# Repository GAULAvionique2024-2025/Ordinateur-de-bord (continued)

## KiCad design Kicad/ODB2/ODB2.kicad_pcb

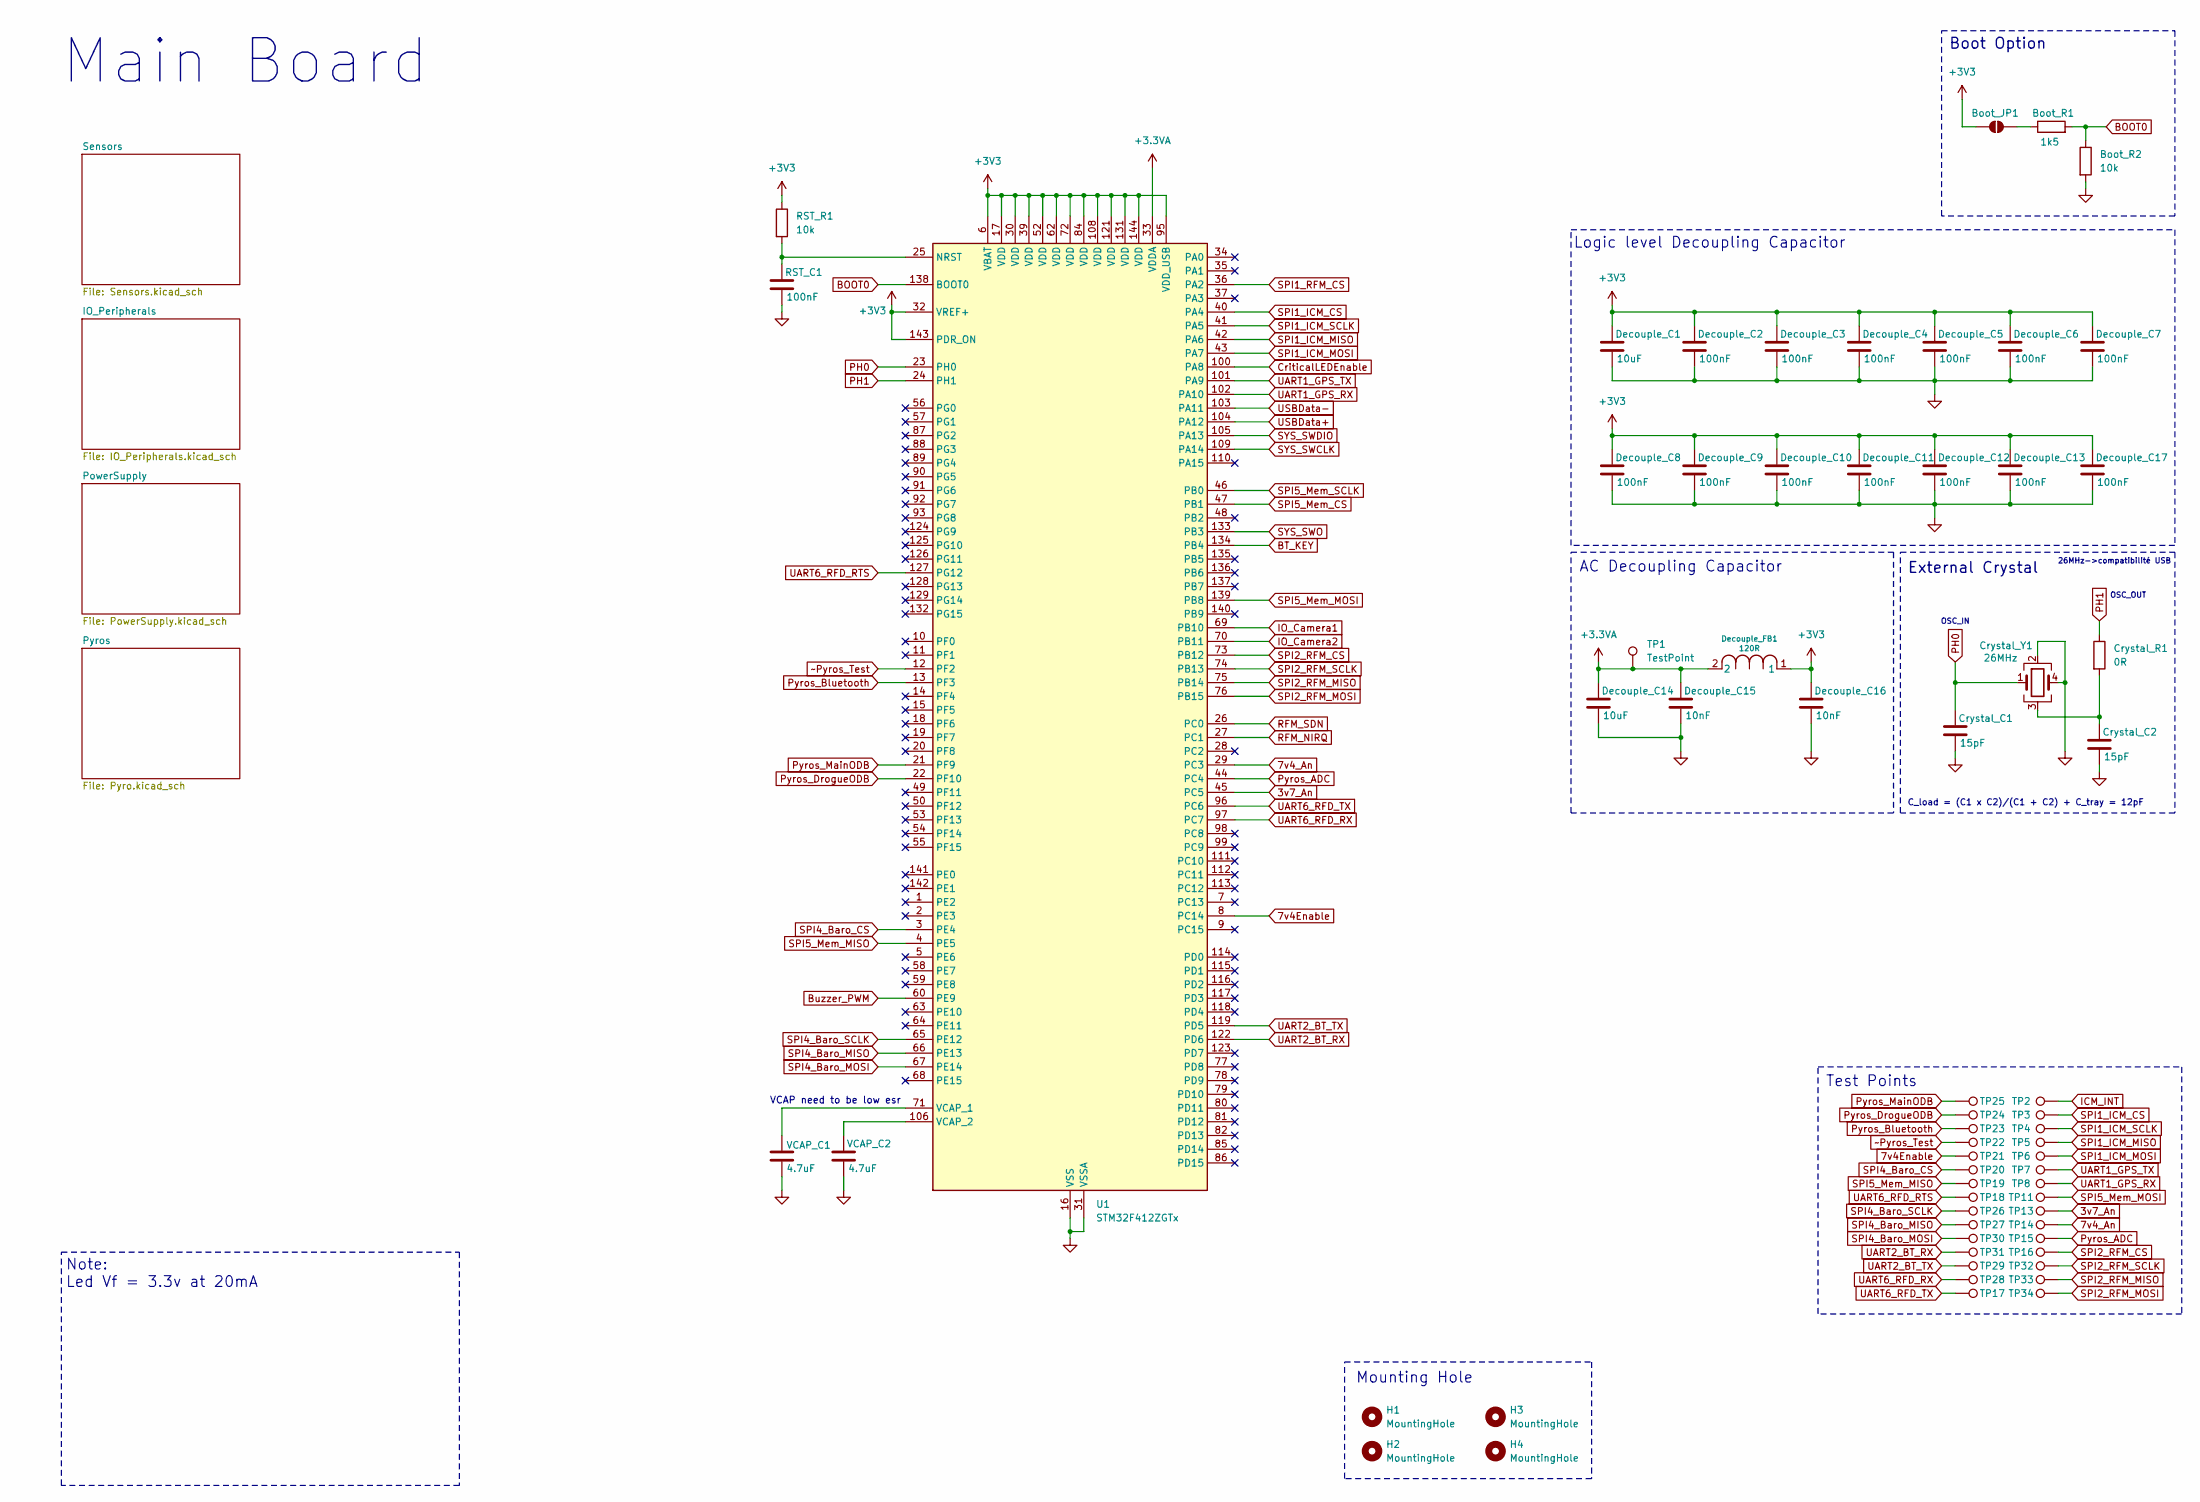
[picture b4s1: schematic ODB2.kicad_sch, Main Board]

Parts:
Boot_JP1: SolderJumper_2_Open; SolderJumper-2_P1.3mm_Open_TrianglePad1.0x1.5mm
Boot_R1: 1k5; R_0603_1608Metric
Boot_R2: 10k; R_0603_1608Metric
Crystal_C1, Crystal_C2: 15pF; C_0603_1608Metric
Crystal_R1: 0R; R_0603_1608Metric
Crystal_Y1: 26MHz; XTAL_TSX-3225_26.0000MF09Z-AC0
Decouple_C1, Decouple_C14: 10uF; C_0603_1608Metric
Decouple_C2, Decouple_C3, Decouple_C4, Decouple_C5, Decouple_C6, Decouple_C7, Decouple_C8, Decouple_C9, Decouple_C10, Decouple_C11, Decouple_C12, Decouple_C13, Decouple_C17: 100nF; C_0603_1608Metric
Decouple_C15, Decouple_C16: 10nF; C_0603_1608Metric
Decouple_FB1: 120R; IND_25_0805_FRT
H1, H2, H3, H4: MountingHole; MountingHole_4.3mm_M4
RST_C1: 100nF; C_0603_1608Metric
RST_R1: 10k; R_0603_1608Metric
TP1, TP2, TP3, TP4, TP5, TP6, TP7, TP8, TP11, TP13, TP14, TP15, TP16, TP17, TP18, TP19, TP20, TP21, TP22, TP23, TP24, TP25, TP26, TP27, TP28, TP29, TP30, TP31, TP32, TP33, TP34: TestPoint; TestPoint_Pad_D1.0mm
U1: STM32F412ZGTx; LQFP-144_20x20mm_P0.5mm
VCAP_C1, VCAP_C2: 4.7uF; C_0603_1608Metric

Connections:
3v7_An: TP13.1, U1.45 (PC5); also elsewhere on the board
7v4Enable: TP21.1, U1.8 (PC14); also elsewhere on the board
7v4_An: TP14.1, U1.29 (PC3); also elsewhere on the board
+3.3VA: Decouple_C14.1, Decouple_C15.1, Decouple_FB1.2, TP1.1, U1.33 (VDDA)
+3V3: Boot_JP1.1 (A), Decouple_C1.1, Decouple_C2.1, Decouple_C3.1, Decouple_C4.1, Decouple_C5.1, Decouple_C6.1, Decouple_C7.1, Decouple_C8.1, Decouple_C9.1, Decouple_C10.1, Decouple_C11.1, Decouple_C12.1, Decouple_C13.1, Decouple_C16.1, Decouple_C17.1, Decouple_FB1.1, RST_R1.1, U1.6 (VBAT), U1.17 (VDD), U1.30 (VDD), U1.32 (VREF+), U1.39 (VDD), U1.52 (VDD), U1.62 (VDD), U1.72 (VDD), U1.84 (VDD), U1.95 (VDD_USB), U1.108 (VDD), U1.121 (VDD), U1.131 (VDD), U1.143 (PDR_ON), U1.144 (VDD); also elsewhere on the board
BOOT0: Boot_R1.2, Boot_R2.1, U1.138 (BOOT0)
BT_KEY: U1.134 (PB4); also elsewhere on the board
Buzzer_PWM: U1.60 (PE9); also elsewhere on the board
CriticalLEDEnable: U1.100 (PA8); also elsewhere on the board
GND: Boot_R2.2, Crystal_C1.2, Crystal_C2.2, Crystal_Y1.2, Crystal_Y1.4, Decouple_C1.2, Decouple_C2.2, Decouple_C3.2, Decouple_C4.2, Decouple_C5.2, Decouple_C6.2, Decouple_C7.2, Decouple_C8.2, Decouple_C9.2, Decouple_C10.2, Decouple_C11.2, Decouple_C12.2, Decouple_C13.2, Decouple_C14.2, Decouple_C15.2, Decouple_C16.2, Decouple_C17.2, RST_C1.2, U1.16 (VSS), U1.31 (VSSA), U1.38 (VSS), U1.51 (VSS), U1.61 (VSS), U1.83 (VSS), U1.94 (VSS), U1.107 (VSS), U1.120 (VSS), U1.130 (VSS), VCAP_C1.2, VCAP_C2.2; also elsewhere on the board
ICM_INT: TP2.1
IO_Camera1: U1.69 (PB10)
IO_Camera2: U1.70 (PB11)
unnamed: Boot_JP1.2 (B), Boot_R1.1
unnamed: Crystal_C2.1, Crystal_R1.2, Crystal_Y1.3
unnamed: RST_C1.1, RST_R1.2, U1.25 (NRST)
unnamed: U1.71 (VCAP_1), VCAP_C1.1
unnamed: U1.106 (VCAP_2), VCAP_C2.1
PH0: Crystal_C1.1, Crystal_Y1.1, U1.23 (PH0)
PH1: Crystal_R1.1, U1.24 (PH1)
Pyros_ADC: TP15.1, U1.44 (PC4); also elsewhere on the board
Pyros_Bluetooth: TP23.1, U1.13 (PF3); also elsewhere on the board
Pyros_DrogueODB: TP24.1, U1.22 (PF10); also elsewhere on the board
Pyros_MainODB: TP25.1, U1.21 (PF9); also elsewhere on the board
RFM_NIRQ: U1.27 (PC1); also elsewhere on the board
RFM_SDN: U1.26 (PC0); also elsewhere on the board
SPI1_ICM_CS: TP3.1, U1.40 (PA4); also elsewhere on the board
SPI1_ICM_MISO: TP5.1, U1.42 (PA6); also elsewhere on the board
SPI1_ICM_MOSI: TP6.1, U1.43 (PA7); also elsewhere on the board
SPI1_ICM_SCLK: TP4.1, U1.41 (PA5); also elsewhere on the board
SPI1_RFM_CS: U1.36 (PA2)
SPI2_RFM_CS: TP16.1, U1.73 (PB12); also elsewhere on the board
SPI2_RFM_MISO: TP33.1, U1.75 (PB14); also elsewhere on the board
SPI2_RFM_MOSI: TP34.1, U1.76 (PB15); also elsewhere on the board
SPI2_RFM_SCLK: TP32.1, U1.74 (PB13); also elsewhere on the board
SPI4_Baro_CS: TP20.1, U1.3 (PE4); also elsewhere on the board
SPI4_Baro_MISO: TP27.1, U1.66 (PE13); also elsewhere on the board
SPI4_Baro_MOSI: TP30.1, U1.67 (PE14); also elsewhere on the board
SPI4_Baro_SCLK: TP26.1, U1.65 (PE12); also elsewhere on the board
SPI5_Mem_CS: U1.47 (PB1); also elsewhere on the board
SPI5_Mem_MISO: TP19.1, U1.4 (PE5); also elsewhere on the board
SPI5_Mem_MOSI: TP11.1, U1.139 (PB8); also elsewhere on the board
SPI5_Mem_SCLK: U1.46 (PB0); also elsewhere on the board
SYS_SWCLK: U1.109 (PA14); also elsewhere on the board
SYS_SWDIO: U1.105 (PA13); also elsewhere on the board
SYS_SWO: U1.133 (PB3); also elsewhere on the board
UART1_GPS_RX: TP8.1, U1.102 (PA10); also elsewhere on the board
UART1_GPS_TX: TP7.1, U1.101 (PA9); also elsewhere on the board
UART2_BT_RX: TP31.1, U1.122 (PD6); also elsewhere on the board
UART2_BT_TX: TP29.1, U1.119 (PD5); also elsewhere on the board
UART6_RFD_RTS: TP18.1, U1.127 (PG12); also elsewhere on the board
UART6_RFD_RX: TP28.1, U1.97 (PC7); also elsewhere on the board
UART6_RFD_TX: TP17.1, U1.96 (PC6); also elsewhere on the board
USBData+: U1.104 (PA12); also elsewhere on the board
USBData-: U1.103 (PA11); also elsewhere on the board
~Pyros_Test: TP22.1, U1.12 (PF2); also elsewhere on the board

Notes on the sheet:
VCAP need to be low esr
26MHz->compatibilité USB
C_load = (C1 x C2)/(C1 + C2) + C_tray = 12pF
Main Board
Mounting Hole
Boot Option
Note: Led Vf = 3.3v at 20mA
AC Decoupling Capacitor
OSC_OUT
Test Points
External Crystal
Logic level Decoupling Capacitor
OSC_IN

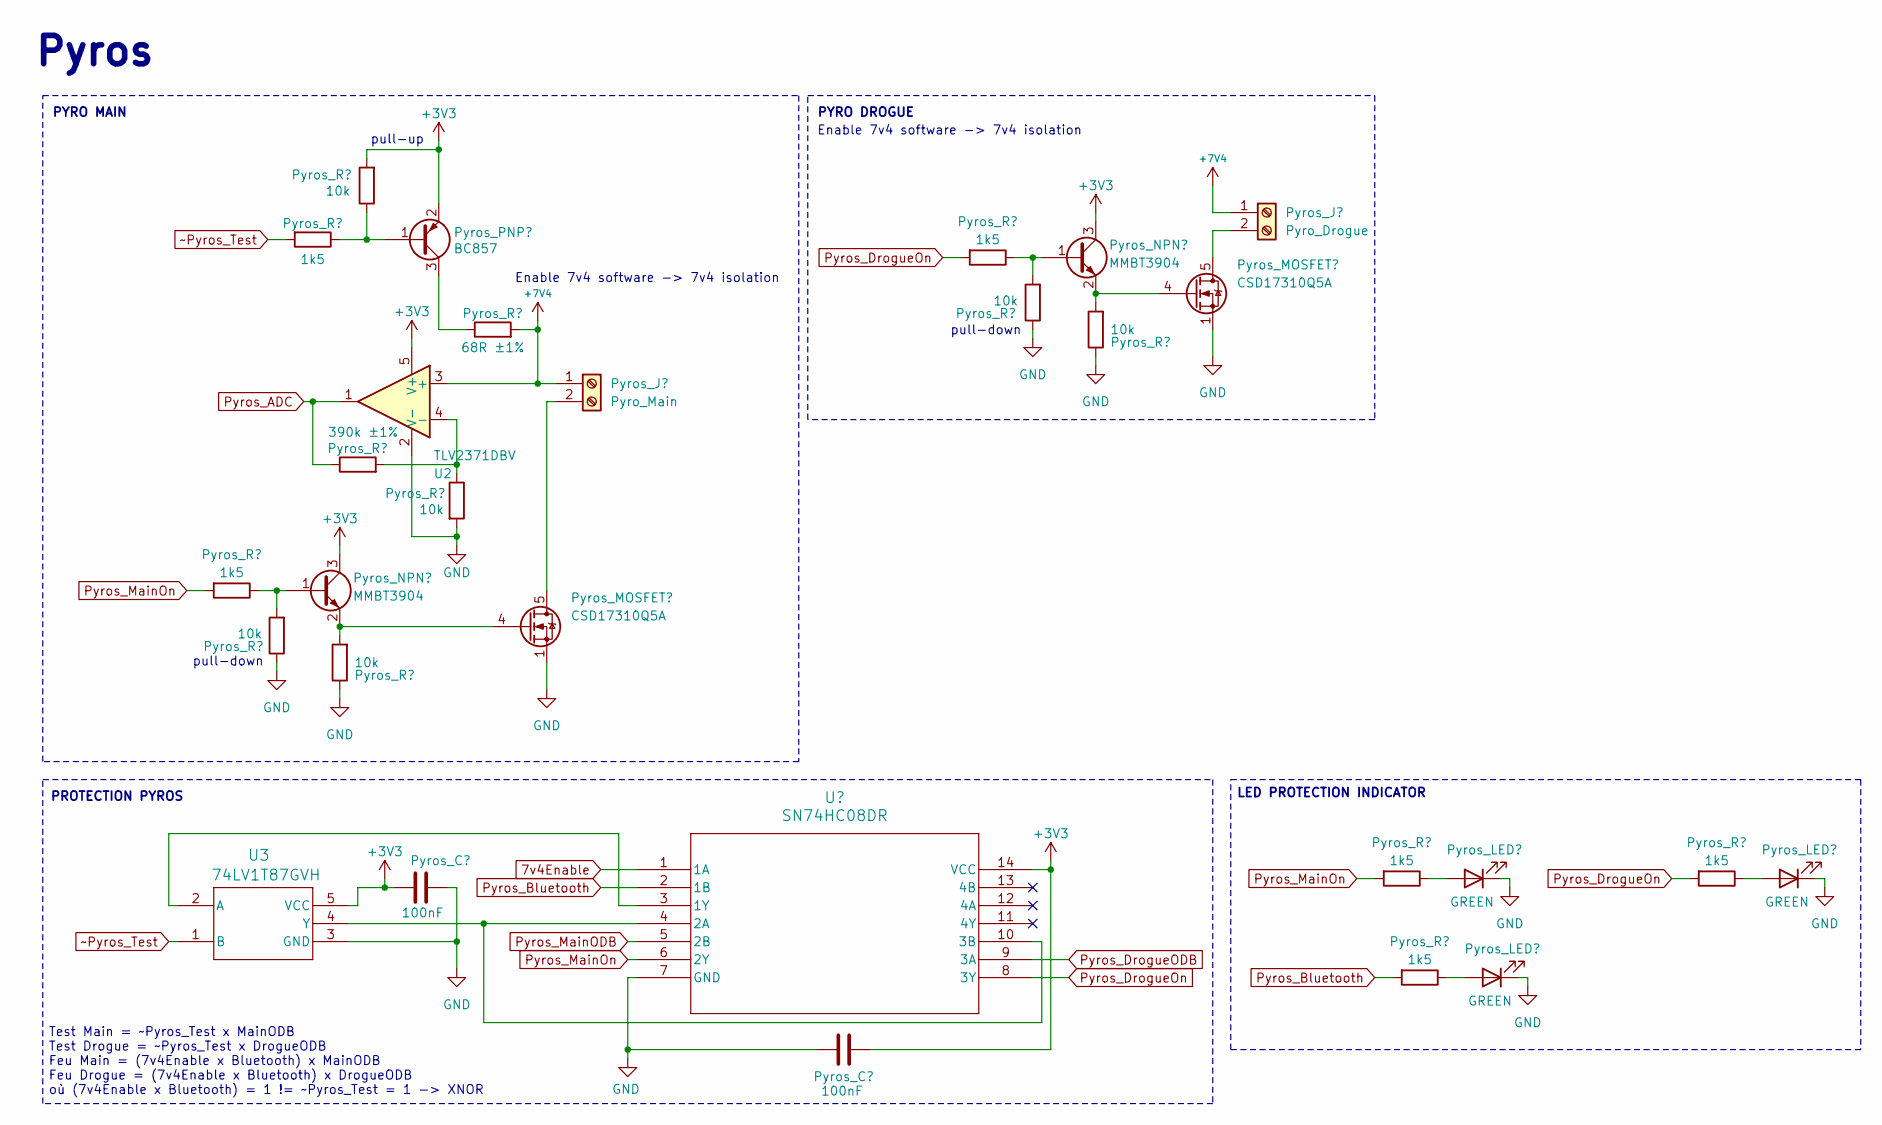
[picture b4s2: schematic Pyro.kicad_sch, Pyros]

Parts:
Pyros_AND1: SN74HC08DR; SOIC-14_3.9x8.7mm_P1.27mm
Pyros_C1, Pyros_C2: 100nF; C_0603_1608Metric
Pyros_J1: Pyro_Main; TerminalBlock_RND_205-00012_1x02_P5.00mm_Horizontal
Pyros_J2: Pyro_Drogue; TerminalBlock_RND_205-00012_1x02_P5.00mm_Horizontal
Pyros_LED1, Pyros_LED2, Pyros_LED4: GREEN; LED_0603_1608Metric
Pyros_MOSFET1, Pyros_MOSFET2: CSD17310Q5A; TDSON-8-1
Pyros_NPN1, Pyros_NPN2: MMBT3904; SOT-23
Pyros_PNP1: BC857; SOT-23
Pyros_R1, Pyros_R6, Pyros_R14, Pyros_R17, Pyros_R18, Pyros_R19: 1k5; R_0603_1608Metric
Pyros_R2, Pyros_R5, Pyros_R7, Pyros_R8, Pyros_R15, Pyros_R16: 10k; R_0603_1608Metric
Pyros_R3: 68R ±1%; R_0603_1608Metric
Pyros_R4: 390k ±1%; R_0603_1608Metric
U2: TLV2371DBV; SOT-23-5
U3: 74LV1T87GVH; SC-74A_SOT753_NEX

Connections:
7v4Enable: Pyros_AND1.1 (1A); also elsewhere on the board
+3V3: Pyros_AND1.14 (VCC), Pyros_C1.2, Pyros_C2.1, Pyros_NPN1.3 (C), Pyros_NPN2.3 (C), Pyros_PNP1.2 (E), Pyros_R2.2, U2.5 (V+), U3.5 (VCC); also elsewhere on the board
+7V4: Pyros_J1.1, Pyros_J2.1, Pyros_R3.2, U2.3 (+); also elsewhere on the board
GND: Pyros_AND1.7 (GND), Pyros_C1.1, Pyros_C2.2, Pyros_LED1.1 (K), Pyros_LED2.1 (K), Pyros_LED4.1 (K), Pyros_MOSFET1.1 (S), Pyros_MOSFET1.2 (S), Pyros_MOSFET1.3 (S), Pyros_MOSFET2.1 (S), Pyros_MOSFET2.2 (S), Pyros_MOSFET2.3 (S), Pyros_R5.2, Pyros_R7.1, Pyros_R8.1, Pyros_R15.1, Pyros_R16.1, U2.2 (V-), U3.3 (GND); also elsewhere on the board
unnamed: Pyros_AND1.3 (1Y), U3.2 (A)
unnamed: Pyros_AND1.4 (2A), Pyros_AND1.10 (3B), U3.4 (Y)
unnamed: Pyros_J1.2, Pyros_MOSFET1.5 (D)
unnamed: Pyros_J2.2, Pyros_MOSFET2.5 (D)
unnamed: Pyros_LED1.2 (A), Pyros_R17.1
unnamed: Pyros_LED2.2 (A), Pyros_R18.1
unnamed: Pyros_LED4.2 (A), Pyros_R19.1
unnamed: Pyros_MOSFET1.4 (G), Pyros_NPN1.2 (E), Pyros_R8.2
unnamed: Pyros_MOSFET2.4 (G), Pyros_NPN2.2 (E), Pyros_R16.2
unnamed: Pyros_NPN1.1 (B), Pyros_R6.1, Pyros_R7.2
unnamed: Pyros_NPN2.1 (B), Pyros_R14.1, Pyros_R15.2
unnamed: Pyros_PNP1.1 (B), Pyros_R1.1, Pyros_R2.1
unnamed: Pyros_PNP1.3 (C), Pyros_R3.1
unnamed: Pyros_R4.2, Pyros_R5.1, U2.4 (-)
Pyros_ADC: Pyros_R4.1, U2.1; also elsewhere on the board
Pyros_Bluetooth: Pyros_AND1.2 (1B), Pyros_R19.2; also elsewhere on the board
Pyros_DrogueODB: Pyros_AND1.9 (3A); also elsewhere on the board
Pyros_DrogueOn: Pyros_AND1.8 (3Y), Pyros_R14.2, Pyros_R18.2
Pyros_MainODB: Pyros_AND1.5 (2B); also elsewhere on the board
Pyros_MainOn: Pyros_AND1.6 (2Y), Pyros_R6.2, Pyros_R17.2
~Pyros_Test: Pyros_R1.2, U3.1 (B); also elsewhere on the board

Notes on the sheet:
PYRO DROGUE
pull-up
Pyros
Enable 7v4 software -> 7v4 isolation
pull-down
LED PROTECTION INDICATOR
PROTECTION PYROS
Test Main = ~Pyros_Test x MainODB Test Drogue = ~Pyros_Test x DrogueODB Feu Main = (7v4Enable x Bluetooth) x MainODB Feu Drogue = (7v4Enable x Bluetooth) x DrogueODB où (7v4Enable x Bluetooth) = 1 != ~Pyros_Test = 1 -> XNOR
PYRO MAIN

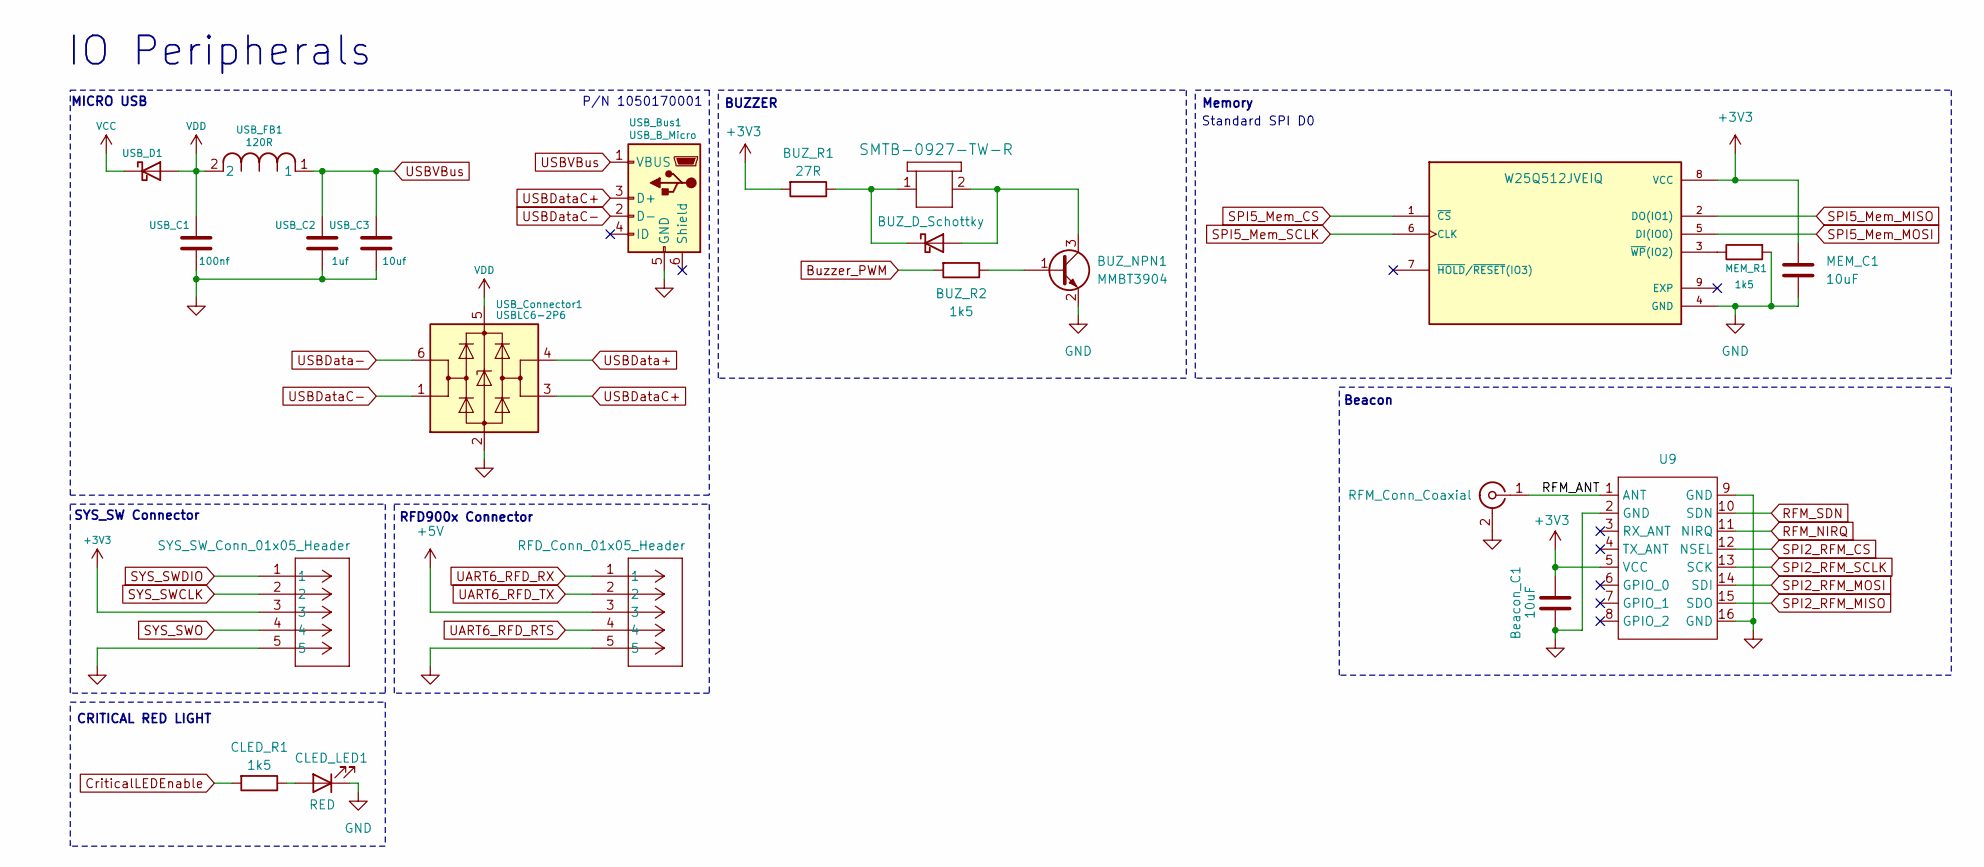
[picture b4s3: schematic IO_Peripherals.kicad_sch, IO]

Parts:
BUZ_Buzzer1: SMTB-0927-TW-R; SMTB-0927-TW-R_PUI
BUZ_NPN1: MMBT3904; SOT-23
BUZ_R1: 27R; R_0603_1608Metric
BUZ_R2: 1k5; R_0603_1608Metric
Beacon_C1: 10uF; C_0603_1608Metric
CLED_LED1: RED; LED_0603_1608Metric
CLED_R1: 1k5; R_0603_1608Metric
D3: BUZ_D_Schottky; D_SOD-123
J3: SYS_SW_Conn_01x05_Header; CONN_SDA-70543-xxxx_05_MOL
J5: RFM_Conn_Coaxial; SMA_Wurth_60312002114503_Vertical
J6: RFD_Conn_01x05_Header; CONN_SDA-70543-xxxx_05_MOL
MEM_C1: 10uF; C_0603_1608Metric
MEM_R1: 1k5; R_0603_1608Metric
U9: RFM22B; RFM22b-S2
U10: W25Q512JVEIQ; SON127P600X800X80-9N; PARTREV G
USB_Bus1: USB_B_Micro; USB_Micro-B_Molex-105017-0001
USB_C1: 100nf; C_0603_1608Metric
USB_C2: 1uf; C_0603_1608Metric
USB_C3: 10uf; C_0603_1608Metric
USB_Connector1: USBLC6-2P6; SOT-666
USB_D1: B260A-13-F; D_SOD-123
USB_FB1: 120R; IND_25_0805_FRT

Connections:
+3V3: BUZ_R1.2, Beacon_C1.2, J3.3, MEM_C1.2, U9.5 (VCC), U10.8 (VCC); also elsewhere on the board
+5V: J6.3; also elsewhere on the board
/IO_Peripherals/RFM_ANT: J5.1 (In), U9.1 (ANT)
Buzzer_PWM: BUZ_R2.2; also elsewhere on the board
CriticalLEDEnable: CLED_R1.2; also elsewhere on the board
GND: BUZ_NPN1.2 (E), Beacon_C1.1, CLED_LED1.1 (K), J3.5, J5.2 (Ext), J6.5, MEM_C1.1, MEM_R1.2, U9.2 (GND), U9.9 (GND), U9.16 (GND), U10.4 (GND), USB_Bus1.5 (GND), USB_C1.1, USB_C2.1, USB_C3.1, USB_Connector1.2 (GND); also elsewhere on the board
unnamed: BUZ_NPN1.1 (B), BUZ_R2.1
unnamed: BUZ_Buzzer1.2, BUZ_NPN1.3 (C), D3.2 (A)
unnamed: CLED_LED1.2 (A), CLED_R1.1
unnamed: BUZ_Buzzer1.1, BUZ_R1.1, D3.1 (K)
unnamed: MEM_R1.1, U10.3 (~WP(IO2))
RFM_NIRQ: U9.11 (NIRQ); also elsewhere on the board
RFM_SDN: U9.10 (SDN); also elsewhere on the board
SPI2_RFM_CS: U9.12 (NSEL); also elsewhere on the board
SPI2_RFM_MISO: U9.15 (SDO); also elsewhere on the board
SPI2_RFM_MOSI: U9.14 (SDI); also elsewhere on the board
SPI2_RFM_SCLK: U9.13 (SCK); also elsewhere on the board
SPI5_Mem_CS: U10.1 (~CS); also elsewhere on the board
SPI5_Mem_MISO: U10.2 (DO(IO1)); also elsewhere on the board
SPI5_Mem_MOSI: U10.5 (DI(IO0)); also elsewhere on the board
SPI5_Mem_SCLK: U10.6 (CLK); also elsewhere on the board
SYS_SWCLK: J3.2; also elsewhere on the board
SYS_SWDIO: J3.1; also elsewhere on the board
SYS_SWO: J3.4; also elsewhere on the board
UART6_RFD_RTS: J6.4; also elsewhere on the board
UART6_RFD_RX: J6.1; also elsewhere on the board
UART6_RFD_TX: J6.2; also elsewhere on the board
USBData+: USB_Connector1.4 (I/O2); also elsewhere on the board
USBData-: USB_Connector1.6 (I/O1); also elsewhere on the board
USBDataC+: USB_Bus1.3 (D+), USB_Connector1.3 (I/O2)
USBDataC-: USB_Bus1.2 (D-), USB_Connector1.1 (I/O1)
USBVBus: USB_Bus1.1 (VBUS), USB_C2.2, USB_C3.2, USB_FB1.1
VCC: USB_D1.1 (K); also elsewhere on the board
VDD: USB_C1.2, USB_Connector1.5 (VBUS), USB_D1.2 (A), USB_FB1.2; also elsewhere on the board

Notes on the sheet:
CRITICAL RED LIGHT
IO Peripherals
Memory
Beacon
MICRO USB
P/N 1050170001
BUZZER
Standard SPI D0
RFD900x Connector
SYS_SW Connector

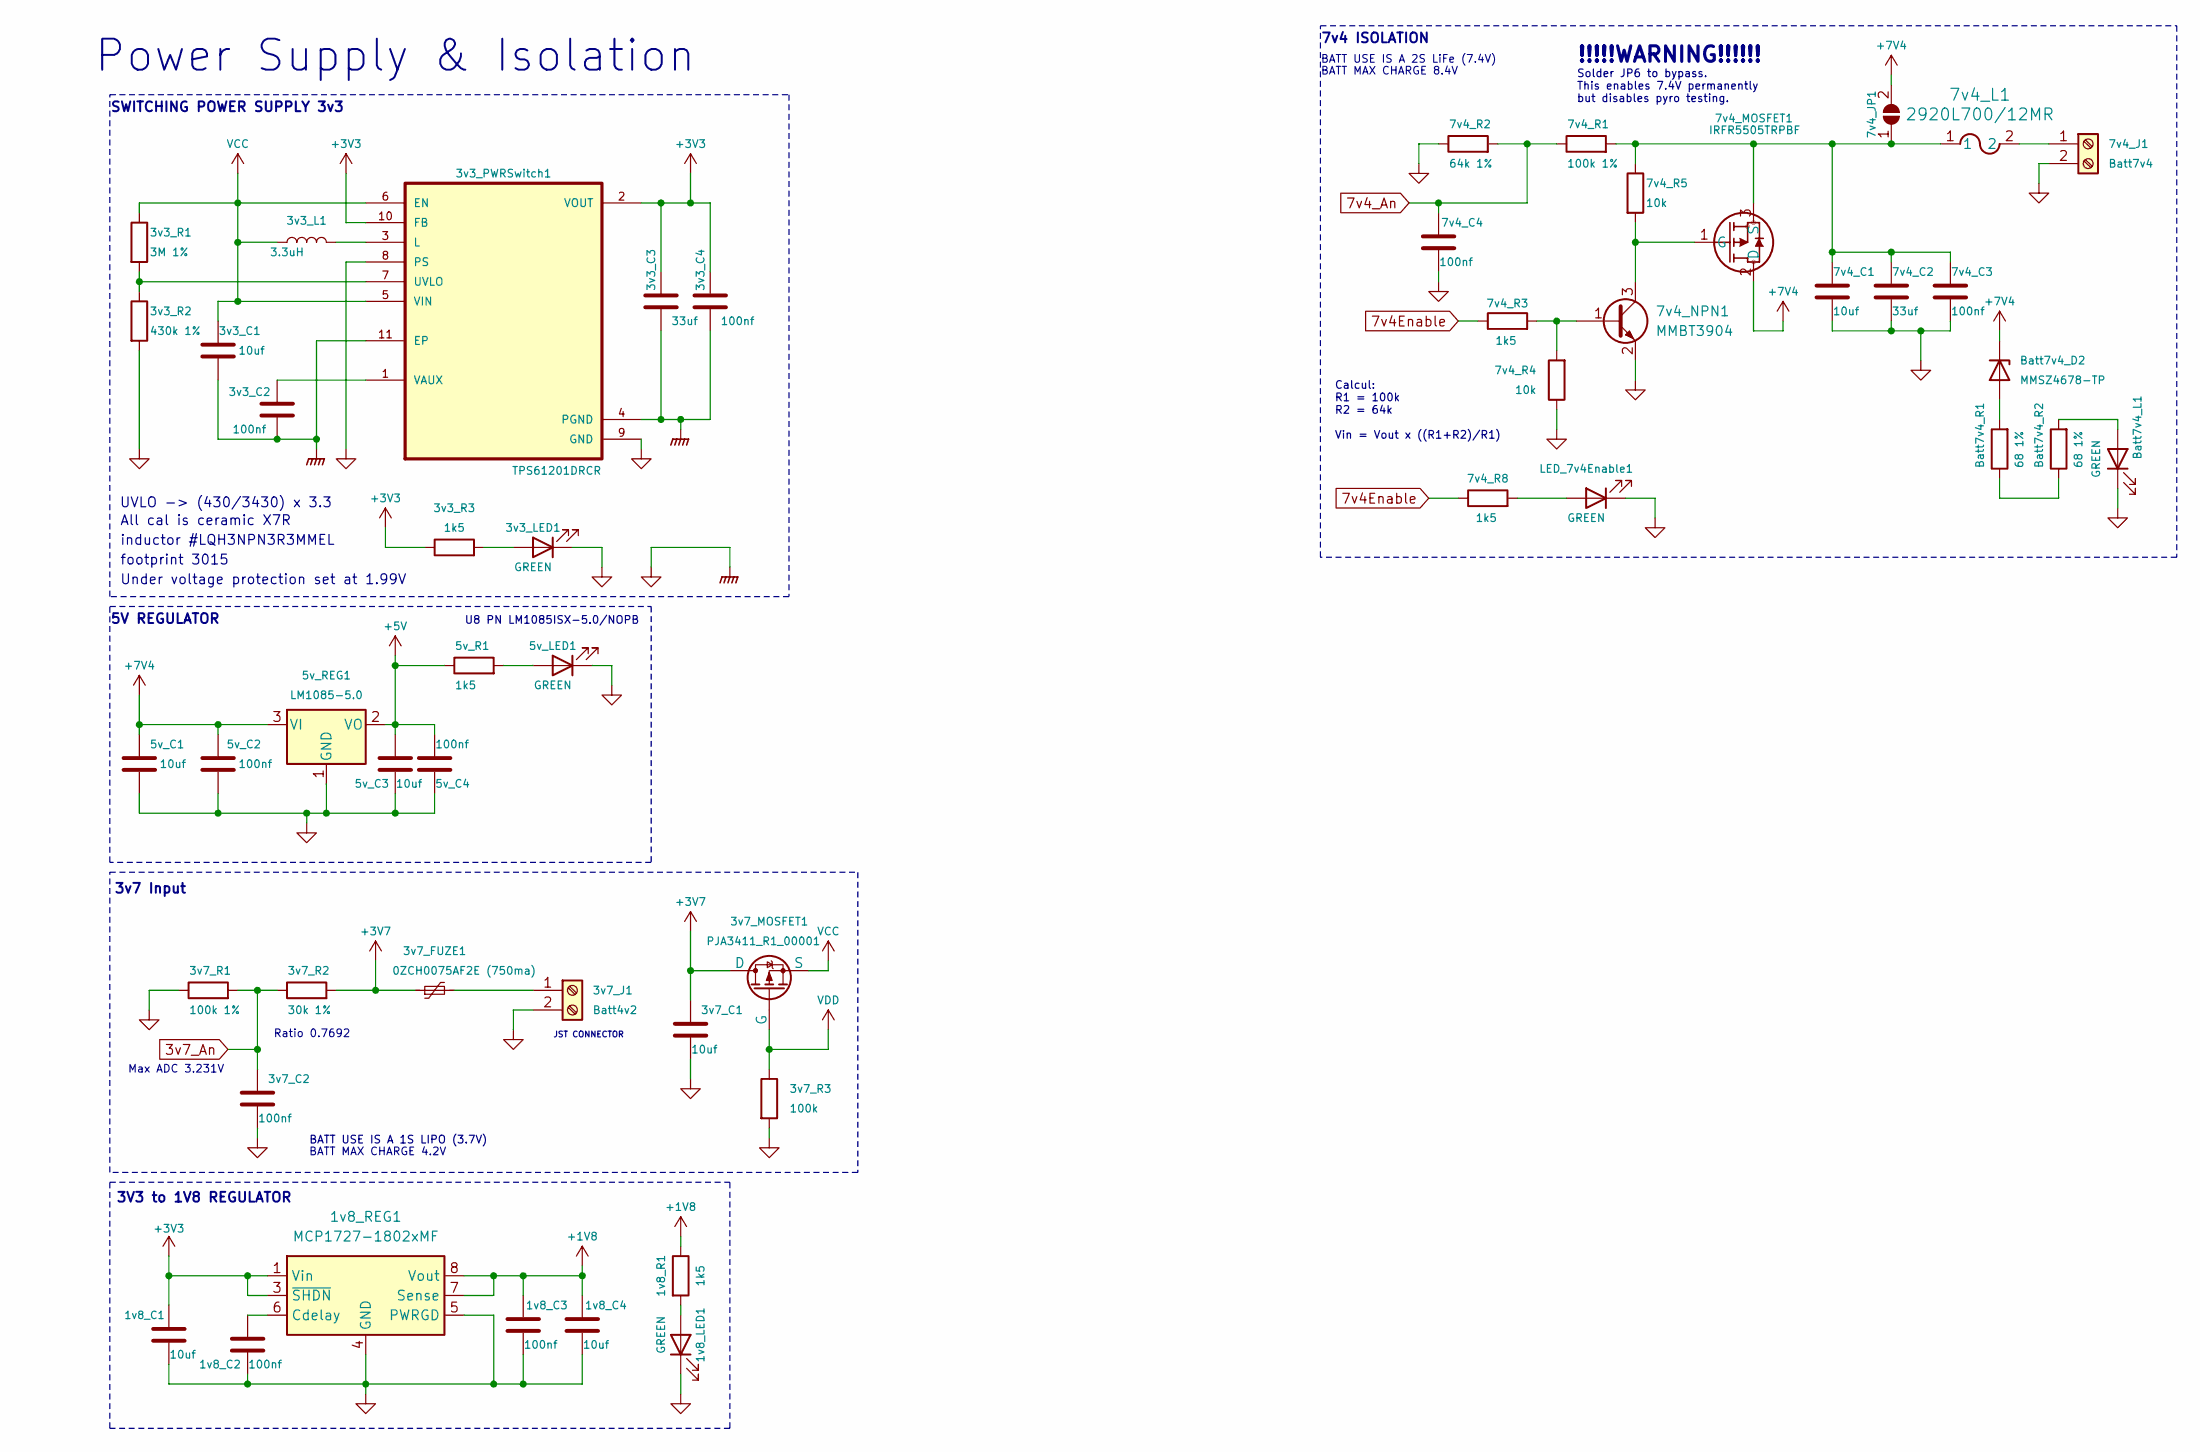
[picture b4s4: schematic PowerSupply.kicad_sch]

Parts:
1v8_C1, 1v8_C4, 3v3_C1, 3v7_C1, 5v_C1, 5v_C3, 7v4_C1: 10uf; C_0603_1608Metric
1v8_C2, 1v8_C3, 3v3_C2, 3v3_C4, 3v7_C2, 5v_C2, 5v_C4, 7v4_C3, 7v4_C4: 100nf; C_0603_1608Metric
1v8_LED1, 3v3_LED1, 5v_LED1: GREEN; LED_0603_1608Metric
1v8_R1, 3v3_R3, 5v_R1, 7v4_R3, 7v4_R8: 1k5; R_0603_1608Metric
1v8_REG1: MCP1727-1802xMF; DFN-8-1EP_3x3mm_P0.65mm_EP1.55x2.4mm
3v3_C3, 7v4_C2: 33uf; C_0603_1608Metric
3v3_L1: 3.3uH; IND_LQH3NPN3R3MMEL
3v3_PWRSwitch1: TPS61201DRCR; VSON-10-1EP_3x3mm_P0.5mm_EP1.65x2.4mm; DigiKey_Part_Number 296-44338-2-ND
3v3_R1: 3M 1%; R_0603_1608Metric
3v3_R2: 430k 1%; R_0603_1608Metric
3v7_FUZE1: 0ZCH0075AF2E (750ma); Fuse_1210_3225Metric
3v7_J1: Batt4v2; SolderWire-1.5sqmm_1x02_P6mm_D1.7mm_OD3mm
3v7_MOSFET1: PJA3411_R1_00001; SOT-23-3
3v7_R1, 7v4_R1: 100k 1%; R_0603_1608Metric
3v7_R2: 30k 1%; R_0603_1608Metric
3v7_R3: 100k; R_0603_1608Metric
5v_REG1: LM1085-5.0; TO-263-3_TabPin2
7v4_J1: Batt7v4; SolderWire-2.5sqmm_1x02_P8.8mm_D2.4mm_OD4.4mm
7v4_JP1: SolderJumper_2_Open; SolderJumper-2_P1.3mm_Open_TrianglePad1.0x1.5mm
7v4_L1: 2920L700/12MR; Fuse_2920_7451Metric
7v4_MOSFET1: IRFR5505TRPBF; PG-TO252AA_INF
7v4_NPN1: MMBT3904; SOT-23
7v4_R2: 64k 1%; R_0603_1608Metric
7v4_R4, 7v4_R5: 10k; R_0603_1608Metric
Batt7v4_D2: MMSZ4678-TP; D_SOD-123
Batt7v4_L1: GREEN; LED_0603_1608Metric
Batt7v4_R1, Batt7v4_R2: 68 1%; R_0603_1608Metric
LED_7v4Enable1: GREEN; LED_0603_1608Metric

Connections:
3v7_An: 3v7_C2.1, 3v7_R1.2, 3v7_R2.1; also elsewhere on the board
7v4Enable: 7v4_R3.1, 7v4_R8.1; also elsewhere on the board
7v4_An: 7v4_C4.1, 7v4_R1.1, 7v4_R2.2; also elsewhere on the board
+3V3: 1v8_C1.1, 1v8_REG1.1 (Vin), 1v8_REG1.2 (Vin), 1v8_REG1.3 (~SHDN), 3v3_C3.1, 3v3_C4.1, 3v3_PWRSwitch1.2 (VOUT), 3v3_PWRSwitch1.10 (FB), 3v3_R3.1; also elsewhere on the board
+3V7: 3v7_C1.1, 3v7_FUZE1.1, 3v7_MOSFET1.3 (D), 3v7_R2.2
+5V: 5v_C3.1, 5v_C4.1, 5v_R1.1, 5v_REG1.2 (VO); also elsewhere on the board
+7V4: 5v_C1.1, 5v_C2.1, 5v_REG1.3 (VI), 7v4_JP1.2 (B), 7v4_MOSFET1.2 (D), Batt7v4_D2.1 (K); also elsewhere on the board
GND: 1v8_C1.2, 1v8_C2.2, 1v8_C3.2, 1v8_C4.2, 1v8_LED1.1 (K), 1v8_REG1.4 (GND), 1v8_REG1.5 (PWRGD), 1v8_REG1.9 (GND), 3v3_C1.2, 3v3_C2.2, 3v3_C3.2, 3v3_C4.2, 3v3_LED1.1 (K), 3v3_PWRSwitch1.4 (PGND), 3v3_PWRSwitch1.8 (PS), 3v3_PWRSwitch1.9 (GND), 3v3_PWRSwitch1.11 (EP), 3v3_R2.2, 3v7_C1.2, 3v7_C2.2, 3v7_J1.2, 3v7_R1.1, 3v7_R3.2, 5v_C1.2, 5v_C2.2, 5v_C3.2, 5v_C4.2, 5v_LED1.1 (K), 5v_REG1.1 (GND), 7v4_C1.2, 7v4_C2.2, 7v4_C3.2, 7v4_C4.2, 7v4_J1.2, 7v4_NPN1.2 (E), 7v4_R2.1, 7v4_R4.1, Batt7v4_L1.1 (K), LED_7v4Enable1.1 (K); also elsewhere on the board
unnamed: 1v8_C2.1, 1v8_REG1.6 (Cdelay)
unnamed: 1v8_C3.1, 1v8_C4.1, 1v8_R1.1, 1v8_REG1.7 (Sense), 1v8_REG1.8 (Vout)
unnamed: 1v8_LED1.2 (A), 1v8_R1.2
unnamed: 3v3_LED1.2 (A), 3v3_R3.2
unnamed: 3v3_L1.2, 3v3_PWRSwitch1.3 (L)
unnamed: 3v3_C2.1, 3v3_PWRSwitch1.1 (VAUX)
unnamed: 3v7_FUZE1.2, 3v7_J1.1
unnamed: 5v_LED1.2 (A), 5v_R1.2
unnamed: 7v4_J1.1, 7v4_L1.2
unnamed: 7v4_C1.1, 7v4_C2.1, 7v4_C3.1, 7v4_JP1.1 (A), 7v4_L1.1, 7v4_MOSFET1.3 (S), 7v4_R1.2, 7v4_R5.1
unnamed 28: 7v4_R8.2, LED_7v4Enable1.2 (A); also elsewhere on the board
unnamed 29: Batt7v4_L1.2 (A), Batt7v4_R2.2; also elsewhere on the board
unnamed: 7v4_MOSFET1.1 (G), 7v4_NPN1.3 (C), 7v4_R5.2
unnamed: 7v4_NPN1.1 (B), 7v4_R3.2, 7v4_R4.2
unnamed: Batt7v4_D2.2 (A), Batt7v4_R1.2
unnamed: Batt7v4_R1.1, Batt7v4_R2.1
VCC: 3v3_C1.1, 3v3_L1.1, 3v3_PWRSwitch1.5 (VIN), 3v3_PWRSwitch1.6 (EN), 3v3_PWRSwitch1.7 (UVLO), 3v3_R1.1, 3v3_R1.2, 3v3_R2.1, 3v7_MOSFET1.2 (S); also elsewhere on the board
VDD: 3v7_MOSFET1.1 (G), 3v7_R3.1; also elsewhere on the board

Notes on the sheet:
Under voltage protection set at 1.99V
Calcul: R1 = 100k R2 = 64k Vin = Vout x ((R1+R2)/R1)
5V REGULATOR
JST CONNECTOR
3v7 Input
U8 PN LM1085ISX-5.0/NOPB
footprint 3015
3V3 to 1V8 REGULATOR
inductor #LQH3NPN3R3MMEL
BATT USE IS A 1S LIPO (3.7V)
7v4 ISOLATION
UVLO -> (430/3430) x 3.3
Max ADC 3.231V
!!!!!WARNING!!!!!!
All cal is ceramic X7R
BATT MAX CHARGE 4.2V
SWITCHING POWER SUPPLY 3v3
Solder JP6 to bypass. This enables 7.4V permanently but disables pyro testing.
BATT USE IS A 2S LiFe (7.4V)
Power Supply & Isolation
Ratio 0.7692
BATT MAX CHARGE 8.4V

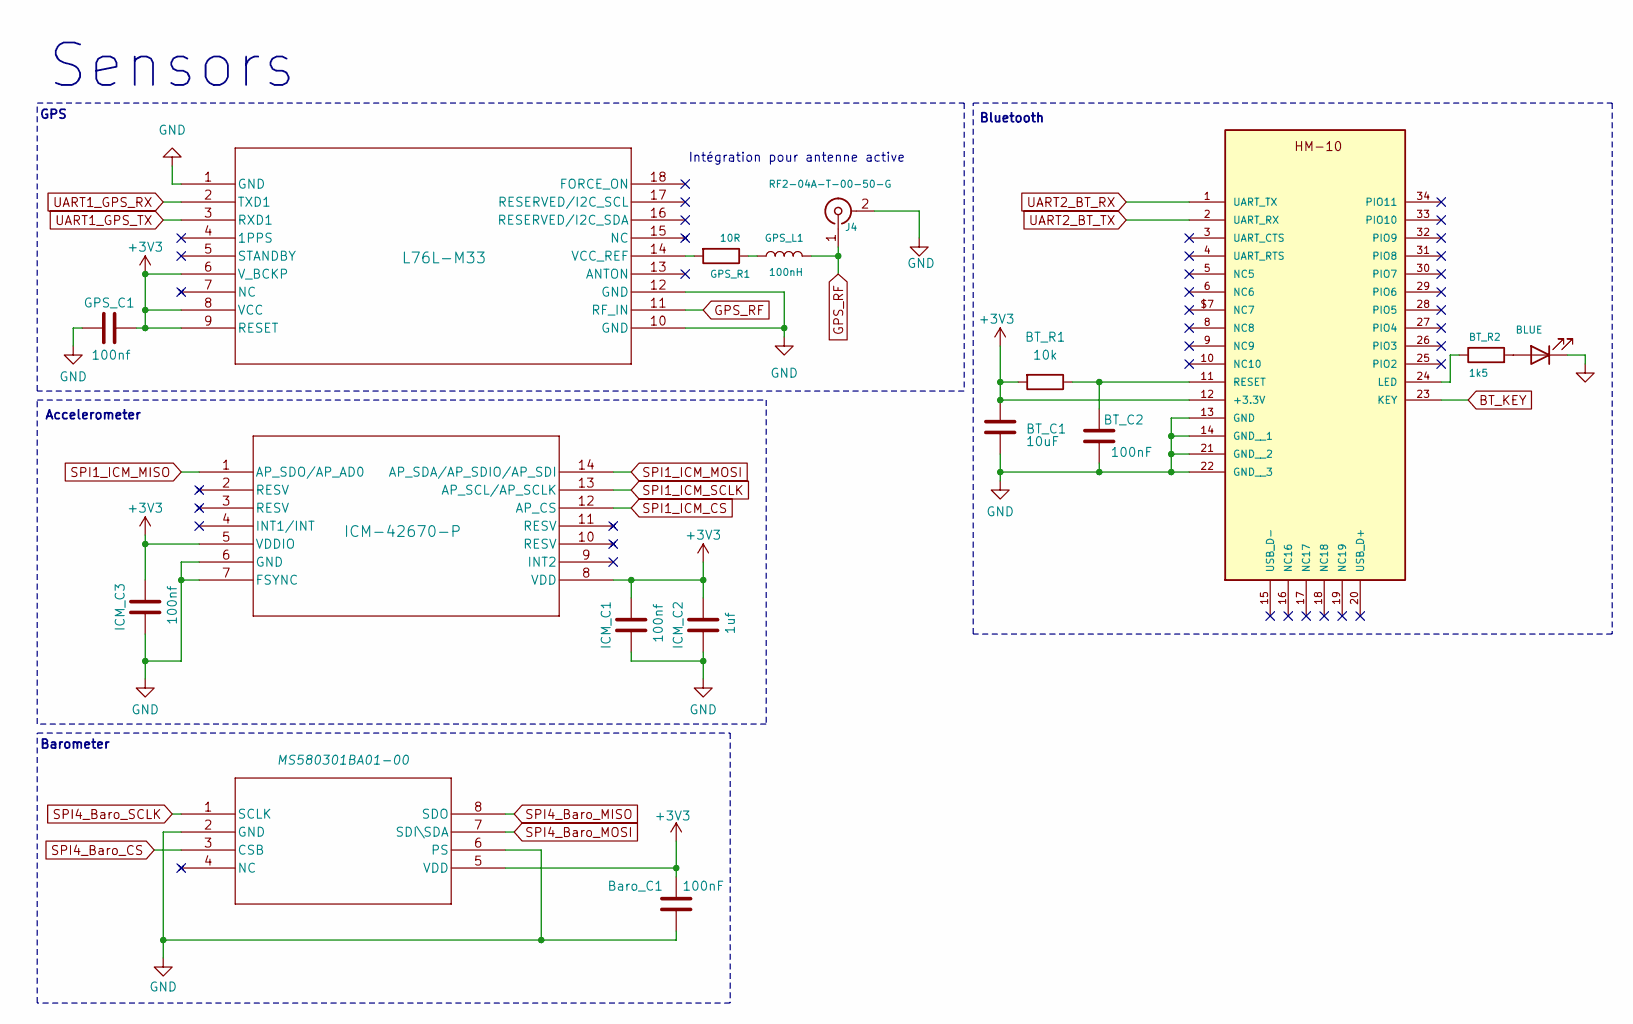
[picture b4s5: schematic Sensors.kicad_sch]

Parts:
BT_C1: 10uF; C_0603_1608Metric
BT_C2: 100nF; C_0603_1608Metric
BT_LED1: BLUE; LED_0603_1608Metric
BT_R1: 10k; R_0603_1608Metric
BT_R2: 1k5; R_0603_1608Metric
Baro_C1: 100nF; C_0603_1608Metric
E1: HM-10
GPS_C1: 100nf; C_0603_1608Metric
GPS_L1: 100nH; L_0603_1608Metric
GPS_R1: 10R; R_0603_1608Metric
ICM_C1, ICM_C3: 100nf; C_0603_1608Metric
ICM_C2: 1uf; C_0603_1608Metric
J4: RF2-04A-T-00-50-G; SMA_Wurth_60312002114503_Vertical
U4: MS580301BA01-00; MS5803-01BA01_TEC
U5: L76L-M33; L76_QWS
U6: ICM-42670-P; LGA14_2.5X3X0.76_IVS

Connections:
+3V3: BT_C1.1, BT_R1.2, Baro_C1.1, E1.12 (+3.3V), GPS_C1.2, ICM_C1.2, ICM_C2.2, ICM_C3.2, U4.5 (VDD), U5.6 (V_BCKP), U5.8 (VCC), U5.9 (RESET), U6.5 (VDDIO), U6.8 (VDD); also elsewhere on the board
BT_KEY: E1.23 (KEY); also elsewhere on the board
GND: BT_C1.2, BT_C2.2, BT_LED1.1 (K), Baro_C1.2, E1.13 (GND), E1.14 (GND__1), E1.21 (GND__2), E1.22 (GND__3), GPS_C1.1, ICM_C1.1, ICM_C2.1, ICM_C3.1, J4.2 (Ext), U4.2 (GND), U4.6 (PS), U5.1 (GND), U5.10 (GND), U5.12 (GND), U6.6 (GND), U6.7 (FSYNC); also elsewhere on the board
GPS_RF: GPS_L1.2, J4.1 (In), U5.11 (RF_IN)
unnamed: BT_LED1.2 (A), BT_R2.2
unnamed: BT_R2.1, E1.24 (LED)
unnamed: BT_C2.1, BT_R1.1, E1.11 (RESET)
unnamed: GPS_L1.1, GPS_R1.1
unnamed: GPS_R1.2, U5.14 (VCC_REF)
SPI1_ICM_CS: U6.12 (AP_CS); also elsewhere on the board
SPI1_ICM_MISO: U6.1 (AP_SDO/AP_AD0); also elsewhere on the board
SPI1_ICM_MOSI: U6.14 (AP_SDA/AP_SDIO/AP_SDI); also elsewhere on the board
SPI1_ICM_SCLK: U6.13 (AP_SCL/AP_SCLK); also elsewhere on the board
SPI4_Baro_CS: U4.3 (CSB); also elsewhere on the board
SPI4_Baro_MISO: U4.8 (SDO); also elsewhere on the board
SPI4_Baro_MOSI: U4.7 (SDI\SDA); also elsewhere on the board
SPI4_Baro_SCLK: U4.1 (SCLK); also elsewhere on the board
UART1_GPS_RX: U5.2 (TXD1); also elsewhere on the board
UART1_GPS_TX: U5.3 (RXD1); also elsewhere on the board
UART2_BT_RX: E1.1 (UART_TX); also elsewhere on the board
UART2_BT_TX: E1.2 (UART_RX); also elsewhere on the board

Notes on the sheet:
Accelerometer
Sensors
GPS
Bluetooth
Barometer
Intégration pour antenne active
